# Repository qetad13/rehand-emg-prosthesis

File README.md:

# ReHand — EMG 기반 손가락 동작 인식 의수 제어 (v2)

> 졸업작품 · **2026.01 – 2026.10** · 4인 팀 (팀장) · v2는 2026-11에 추가

전완부 표면 근전도(sEMG) 4채널을 XIAO ESP32-S3로 1 kHz 샘플링하고, **보드 위에서 직접 추론**해 손가락 동작 8가지를 분류한 뒤 ESP-NOW로 의수 보드에 명령과 힘 세기를 보내는 시스템입니다.

이 브랜치(`v2-only`)에는 **스트리밍 특징 + 1D CNN(TCN)** 방식인 v2 파일만 있습니다.

| 브랜치 | 판단 방식 | 내용 |
|---|---|---|
| [`v2-only`](https://github.com/qetad13/rehand-emg-prosthesis/tree/v2-only) | 스트리밍 특징 + 1D CNN(TCN) | v2 파일만 있음 (지금 보고 있는 내용) |
| [`v1-stft-cnn`](https://github.com/qetad13/rehand-emg-prosthesis/tree/v1-stft-cnn) | STFT 스펙트로그램 + 2D CNN | 기존 버전만 있음 |
| [`main`](https://github.com/qetad13/rehand-emg-prosthesis) | 둘 다 | 기존 버전 위에 v2 추가 |

| 항목 | 내용 |
|---|---|
| 입력 | 표면 EMG 4채널, 1000 Hz, 12-bit ADC |
| 출력 | 휴식 / 엄지 / 검지 / 중지 / 약지 / 소지 / 주먹 / 집게 (8클래스) + 힘 세기 1~100 |
| MCU | Seeed XIAO ESP32-S3 (듀얼코어, 샘플링·추론 코어 분리) |
| 모델 | 25 ms마다 계산하는 특징 22개 + 과거만 보는 1D 합성곱 3층, 가중치 5,960개 |
| 통신 | ESP-NOW 양방향 (근전도 보드 ↔ 의수 보드 직접 연결, 자동 페어링) |
| 성능 | 미사용 순서 세션 기준 창 단위 정확도 **98.7%**, 실시간 제어 지연 중앙값 **226 ms** (25 ms마다 판단) |

> **실제 보드·의수에서의 동작 시험은 아직 하지 않았습니다.** 컴파일과 PC 대조 검증까지만 확인했습니다.
> 처음 올릴 때는 [docs/v2_guide.md](docs/v2_guide.md)의 "처음 올릴 때 확인 순서"를 따라 주세요.

사용 방법: [docs/v2_guide.md](docs/v2_guide.md) · 실험과 결과: [docs/v2_results.md](docs/v2_results.md)

---

## 시스템 구조

```mermaid
flowchart LR
    subgraph Arm["전완부"]
        S1[EMG 센서 ×4]
    end
    subgraph EMG["근전도 보드 (자체 PCB + XIAO ESP32-S3)"]
        ADC["ADC 1 kHz<br/>(Core 1)"] --> F["IIR 필터<br/>HPF 20 Hz + Notch 60 Hz"]
        F --> HOP["25 ms 누적값<br/>(크기 · 차분 · 영교차 · 채널 상관)"]
        HOP -->|큐| INF["특징 22개 → TCN 추론<br/>(Core 0, FreeRTOS task)"]
        INF --> V["확률 평활 + 문턱 + 휴식 게이트<br/>(오작동 억제)"]
        INF --> ST["힘 세기<br/>(최근 0.2초 크기 / 휴식 크기)"]
    end
    subgraph Hand["의수 보드 (XIAO ESP32-S3 + 서보 ×7)"]
        R[ESP-NOW 송수신] --> SV["서보 제어<br/>(힘 세기 → 속도 · 쥐는 힘)"]
    end
    S1 -->|Molex SPOX 3핀| ADC
    V -->|명령 1~8| R
    ST -->|힘 세기 1~100| R
    R -.->|"상태 (호밍 · 과열 · 전압)"| V

    subgraph PC["PC (오프라인)"]
        GUI["수집 GUI<br/>(PySide6)"] --> CSV[(CSV + 라벨 순서)]
        CSV --> TR["PyTorch 학습<br/>train_v2.py"]
        TR -->|"emg2_model.h<br/>emg2_test_vectors.h"| INF
        TR --> HC["host_check.py<br/>(C 코드 ↔ PyTorch 대조)"]
    end
    ADC -.->|MODE_RECORD, USB 시리얼| GUI
```

### 데이터 파이프라인

1. **수집** — 펌웨어를 `MODE_RECORD`로 올리고 GUI가 5초 힘주기 / 5초 쉬기를 안내하며 녹화 (1세션 = 8동작 × 10초 = 80초)
2. **전처리** — 4차 Butterworth HPF 20 Hz + 60 Hz 노치 (PC와 ESP32에서 **같은 SOS 계수**로 계산)
3. **특징** — 25 ms마다 채널별 로그 진폭(휴식 대비) · 주파수 비 2개 · 영교차율과 채널 쌍 상관 6개 = 22개. STFT 없이 누적합만으로 계산
4. **모델** — 과거만 보는 1D 합성곱 3층(폭 24/24/32, 커널 3, 팽창 1/2/4). 최근 0.375초를 보고 25 ms마다 확률 출력. 층마다 지난 결과를 버퍼에 두고 새 프레임만 계산
5. **라벨** — 화면 지시 시각이 아니라 근전도가 실제로 올라온·내려간 시점 기준. 전환 구간은 학습에서 제외
6. **출력 규칙** — 평활한 확률이 0.8 이상이면 켜기, 휴식 3번 연속이면 끄기, 최소 유지 0.1초, 휴식 게이트 1.5배. 손가락 → 다른 손가락은 휴식을 거쳐야 하고 주먹만 예외
7. **내보내기** — 가중치·필터 계수·판단 규칙을 C 헤더로 생성하고, PC 예측값을 테스트 벡터로 함께 내보냄

---

## 폴더 구조

```
rehand-emg-prosthesis/
├─ hardware/                 KiCad 프로젝트 (근전도 보드)
│  ├─ v1/                    초기 보드: 회로도 · PCB · gerber/
│  └─ v2/                    현재 보드 (배터리 · 버튼 추가): 회로도 · PCB · gerber/
├─ collector/                데이터 수집 GUI (PySide6 + pyserial)
│  └─ emg_collector_v4.py
├─ training/                 학습 + ESP32용 C 헤더 생성
│  ├─ train_v2.py            학습: python train_v2.py --cv
│  ├─ emg_data.py            데이터 읽기 · 필터 · 실시간 지표 (train_v2.py가 사용)
│  ├─ host_check.py          펌웨어 C 코드를 PC에서 PyTorch와 대조
│  ├─ data/Fixed/            고정 순서 세션 15개 (학습 / 교차검증)
│  ├─ data/Random/           무작위 순서 세션 5개 (시험 전용)
│  └─ output_v2/             학습 결과 (report, 그림, 모델)
├─ firmware/                 Arduino (XIAO ESP32-S3)
│  ├─ emg_board_v2/          근전도 보드: 녹화 · 점검 · 실시간 판단 · 재생 · 자가 점검
│  └─ hand_board_v2/         의수 보드: 자세 표 · 힘 세기 비례 제어 · 호밍 · 서보 감시
└─ docs/
   ├─ v2_guide.md            사용 안내
   ├─ v2_results.md          결과와 실험 기록
   └─ images/                결과 그림 · 회로도
```

`hardware/v1`, `hardware/v2`는 PCB 버전이고, 판단 방식의 v1/v2와는 관계가 없습니다.

---

## 하드웨어

<p align="center">

  <br><sub>왼쪽 PCB v1 · 오른쪽 PCB v2 (현재)</sub>
</p>

| | PCB v1 | PCB v2 (현재) |
|---|---|---|
| 크기 | 28.75 × 40 mm | 33.2 × 40 mm |
| MCU 실장 | XIAO ESP32-S3 DIP 풋프린트 | XIAO ESP32-S3 **SMD** 풋프린트 (하단 BAT 패드 사용) |
| 센서 입력 | Molex SPOX 3핀 ×4 (신호 / 3V3 / GND → A0~A3) | 동일 |
| 전원 | USB | **J5 PicoBlade 2핀** → XIAO BAT 패드 (배터리 연결) |
| 입력 버튼 | 없음 | **SW1 · SW2** (D7 · D8), 풀업 저항 + 디바운스 커패시터 (0805) |
| 회로도 | [schematic_v1.svg](docs/images/schematic_v1.svg) | [schematic_v2.svg](docs/images/schematic_v2.svg) |

버튼 동작 (자세한 내용과 LED 표시는 [docs/v2_guide.md](docs/v2_guide.md)):

| 버튼 | 짧게 | 3초 |
|---|---|---|
| SW1 | 근전도 모드 ↔ 매크로 모드 (뗄 때 바뀜) | 사용자 보정 시작 |
| SW2 | 근전도 모드: 잠금 켜기/끄기 · 매크로 모드: 다음 동작 | 의수 호밍 |

스위치가 없는 보드에서는 시리얼 키(`1 2 h c x l ?`)나 BOOT 버튼으로 대신 조작합니다.

---

## 성능

평가는 **학습에 쓰지 않은 Random 세션 5개**(동작 순서를 무작위로 섞어 녹화, 총 6.7분)로 했습니다. 설정은 고정 순서 15세션의 5겹 교차검증만으로 골랐습니다. 비교 대상 v1은 [`v1-stft-cnn`](https://github.com/qetad13/rehand-emg-prosthesis/tree/v1-stft-cnn) 브랜치의 STFT + 2D CNN 방식입니다.

| Random 5세션 | v1 | v2 (이 브랜치) |
|---|---|---|
| 창 단위 정확도 (8클래스) | 96.4% | **98.7%** |
| 창 단위 정확도 (휴식 제외 7동작) | 95.1% | **97.7%** |
| 수축 구간 다수결 | 38/40 | 39/40 |
| 근전도 시작 → 올바른 출력 (중앙값 / 90%) | 356 / 820 ms | **226** / 744 ms |
| 힘 뺀 뒤 출력 해제 (중앙값) | 169 ms | **94 ms** |
| 동작 인식 성공 / 놓침 | 34 / 1 | 35 / 0 |
| 잘못된 손가락 출력 (6.7분) | 3회 | 1회 |
| 휴식 중 오작동 비율 | 0.1% | 0.26% |
| 판단 주기 | 100 ms | 25 ms |
| 1초당 곱셈 수 | 약 300만 | 약 23만 |

클래스별: 휴식 100%, 엄지 100%, 검지 100%, 중지 99%, 약지 100%, 소지 99%, 주먹 100%, 집게 86%

| 교차검증 (고정 순서 15세션, 20분) | v1 | v2 |
|---|---|---|
| 창 단위 정확도 | 97.6% | **99.1%** |
| 제어 지연 중앙값 / 90% | 298 / 586 ms | **220 / 471 ms** |
| 인식 성공 / 놓침 | 100 / 4 | 104 / 0 |
| 잘못된 손가락 출력 | 28회 | **3회** |
| 휴식 중 오작동 비율 | 0.52% | 0.09% |

알아 둘 점

- 휴식 중 오작동 비율은 Random에서 v1보다 조금 높습니다 (교차검증에서는 낮음).
- 집게가 86%로 가장 약합니다.
- 20세션이 모두 한 번 붙인 상태에서 녹화되어, 전극을 다시 붙였을 때의 성능은 확인하지 못했습니다. 이를 줄이기 위해 사용자 보정(약 40초)을 넣었습니다.
- 지연에는 무선 전송과 서보 반응 시간이 포함되어 있지 않습니다.

실험 내용(특징별 기여, 힘 세기 변화, 보정 효과)은 [docs/v2_results.md](docs/v2_results.md)에 있습니다.

---

## 주요 기능

- **근전도 보드** ([firmware/emg_board_v2](firmware/emg_board_v2))
  - 모드 5개: 녹화(`MODE_RECORD`) · 센서 점검(`MODE_CHECK`) · 실시간 판단(`MODE_RUN`) · 저장 데이터 재생(`MODE_REPLAY`) · 자가 점검(`MODE_SELFTEST`)
  - 사용자 보정: 의수가 동작을 하나씩 보여 주면 따라 하는 방식으로 채널별 이득과 동작별 힘 기준을 다시 맞추고 보드에 저장
  - 잠금 모드: 쥔 상태를 유지한 채 힘을 빼도 풀리지 않게 함
  - 의수 상태(연결 · 호밍 중 · 과열 · 전압 · 서보 응답)를 LED로 표시
- **의수 보드** ([firmware/hand_board_v2](firmware/hand_board_v2))
  - 힘 세기에 비례한 속도와 쥐는 힘, 움직이는 동안 계속 반영
  - "네 손가락 먼저 → 엄지" 순서를 기다리는 동안에도 명령과 무선 수신이 멈추지 않음
  - 호밍을 별도 태스크로 분리, 자세를 표 한 줄로 추가·수정
  - 서보 온도 · 전압 · 응답을 감시해 근전도 보드에 알림
  - 처음 연결된 근전도 보드의 주소를 저장하고 다른 송신기의 명령은 무시 (시리얼 `p` 또는 BOOT 3초로 해제, 암호화는 없음)
- **PC 대조 검증** ([training/host_check.py](training/host_check.py))
  - 펌웨어의 `emg2.cpp`를 PC에서 그대로 컴파일해 Random 세션 전체(32,014프레임)를 PyTorch와 비교: 확률 차이 최대 8.3e-07, 최종 출력 차이 0

---

## 실행 방법

### 1. 설치
```bash
pip install -r training/requirements.txt -r collector/requirements.txt
```

### 2. 데이터 수집
1. `firmware/emg_board_v2/emg_board_v2.ino`에서 `#define RUN_MODE MODE_CHECK`로 업로드 → 채널 상태 확인
2. `MODE_RECORD`로 업로드 후 `python collector/emg_collector_v4.py`
3. 고정 순서는 `training/data/Fixed/`, 무작위 순서는 `training/data/Random/`에 저장 (순서는 `_order.txt`로 자동 기록)

### 3. 학습과 검증
```bash
python training/train_v2.py --cv
```
```bash
python training/host_check.py
```
`emg2_model.h`, `emg2_test_vectors.h`가 `firmware/emg_board_v2`에 자동 복사됩니다. `host_check.py`는 C++ 컴파일러가 필요합니다 (없으면 `pip install ziglang`).

### 4. 업로드
| 스케치 | 용도 |
|---|---|
| `emg_board_v2` (`MODE_SELFTEST`) | PC 결과와 일치 여부 확인 (`8 / 8 통과`), 판단 1회 계산 시간 |
| `emg_board_v2` (`MODE_RUN`) | 실시간 판단 + ESP-NOW 전송 |
| `emg_board_v2` (`MODE_REPLAY`) | 센서 없이 저장 데이터로 판단 흐름 확인 |
| `hand_board_v2` | 의수 제어 (시리얼에서 `숫자`, `s숫자`, `?`로 단독 시험) |

Arduino IDE 설정: 보드 `XIAO_ESP32S3`, `USB CDC On Boot: Enabled`

---

## 변경 이력

| 날짜 | 변경 내용 |
|---|---|
| 2026-11-12 | **연결 상대 고정**: 의수가 처음 연결된 근전도 보드의 주소를 저장하고 다른 송신기의 명령은 무시. 의수 시리얼 `p` 또는 BOOT 3초로 해제. 암호화는 아직 없음 ([#1](https://github.com/qetad13/rehand-emg-prosthesis/issues/1)) |
| 2026-11-12 | **v2**: 스트리밍 특징 + TCN 판단 방식(`train_v2.py`, `emg_board_v2`), 의수 보드 v2(`hand_board_v2`: 힘 세기 비례 제어, 양방향 연결, 호밍 태스크), 사용자 보정, 잠금 모드, PC 대조 검증(`host_check.py`) |
| 2026-09-30 | **PCB v2**: XIAO SMD 실장, 배터리 커넥터, 버튼 2개(풀업 + RC 디바운스) 추가 |

그 전의 개발 과정과 트러블슈팅 기록은 [`v1-stft-cnn`](https://github.com/qetad13/rehand-emg-prosthesis/tree/v1-stft-cnn) 브랜치의 README에 있습니다.

---

## 기술 스택
`Python` `PyTorch` `NumPy/SciPy` `PySide6` · `C/C++ (Arduino, FreeRTOS)` · `KiCad`

## 연락처

| 항목 | 내용 |
|---|---|
| 소속 | 전자공학과 |
| 이메일 | [kjoonh1@gmail.com](mailto:kjoonh1@gmail.com) |
| GitHub | [@qetad13](https://github.com/qetad13) |

## 라이선스 / 출처
- [MIT License](LICENSE) (아래 외부 코드는 각 원본 라이선스를 따름)
- `firmware/emg_board_v2/EMGFilters.*`: OYMotion Inc. (BSD-3-Clause), 채널별 상태 분리 수정

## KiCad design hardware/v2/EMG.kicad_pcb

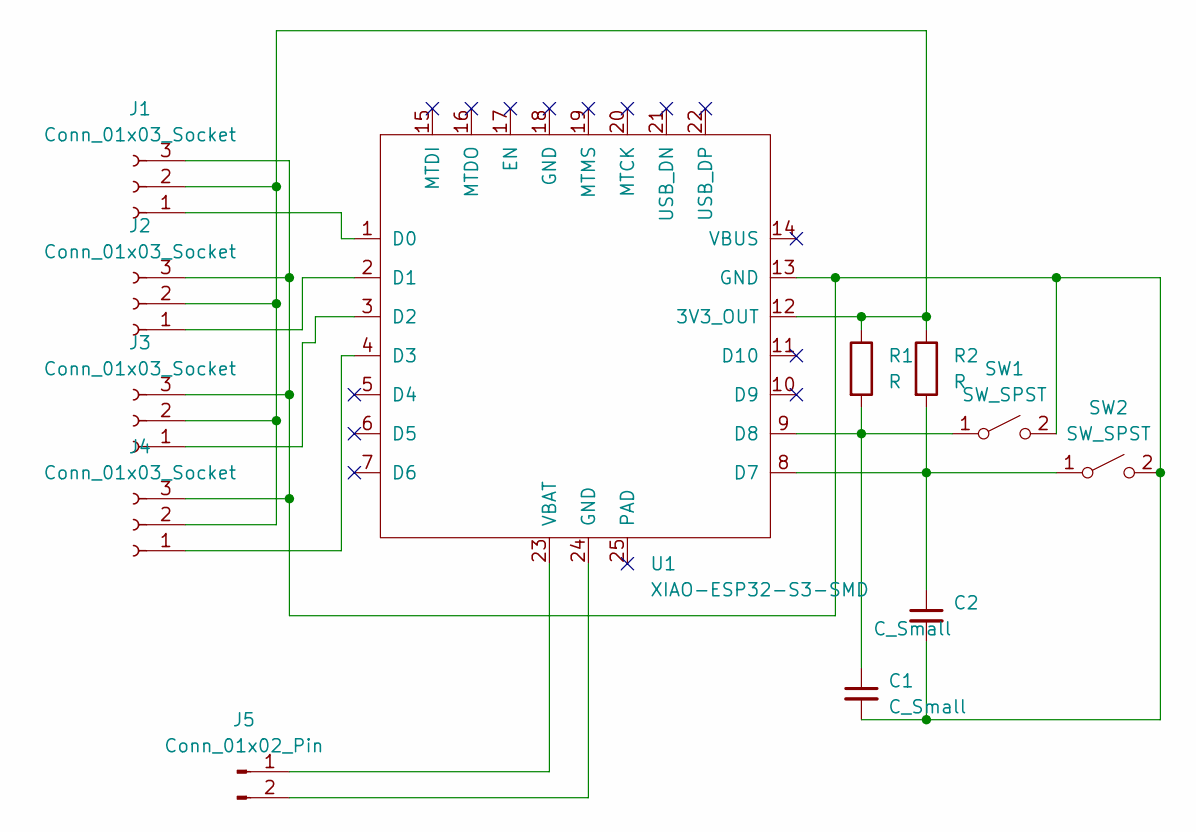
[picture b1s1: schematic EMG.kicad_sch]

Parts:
C1, C2: C_Small; C_0805_2012Metric
J1, J2, J3, J4: Conn_01x03_Socket; Molex_SPOX_5267-03A_1x03_P2.50mm_Vertical
J5: Conn_01x02_Pin; Molex_PicoBlade_53261-0271_1x02-1MP_P1.25mm_Horizontal
R1, R2: R; R_0805_2012Metric
SW1, SW2: SW_SPST; PinHeader_1x02_P2.54mm_Vertical
U1: XIAO-ESP32-S3-SMD

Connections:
unnamed: J1.1, U1.1 (D0)
unnamed 1: J1.2, J2.2, J3.2, J4.2, R1.1, R2.1, U1.12 (3V3_OUT); also elsewhere on the board
unnamed: C1.2, C2.2, J1.3, J2.3, J3.3, J4.3, SW1.2 (B), SW2.2 (B), U1.13 (GND)
unnamed: J2.1, U1.2 (D1)
unnamed: J3.1, U1.3 (D2)
unnamed: J4.1, U1.4 (D3)
unnamed: J5.1, U1.23 (VBAT)
unnamed: J5.2, U1.24 (GND)
unnamed 8: C1.1, R1.2, SW1.1 (A), U1.9 (D8); also elsewhere on the board
unnamed: C2.1, R2.2, SW2.1 (A), U1.8 (D7)

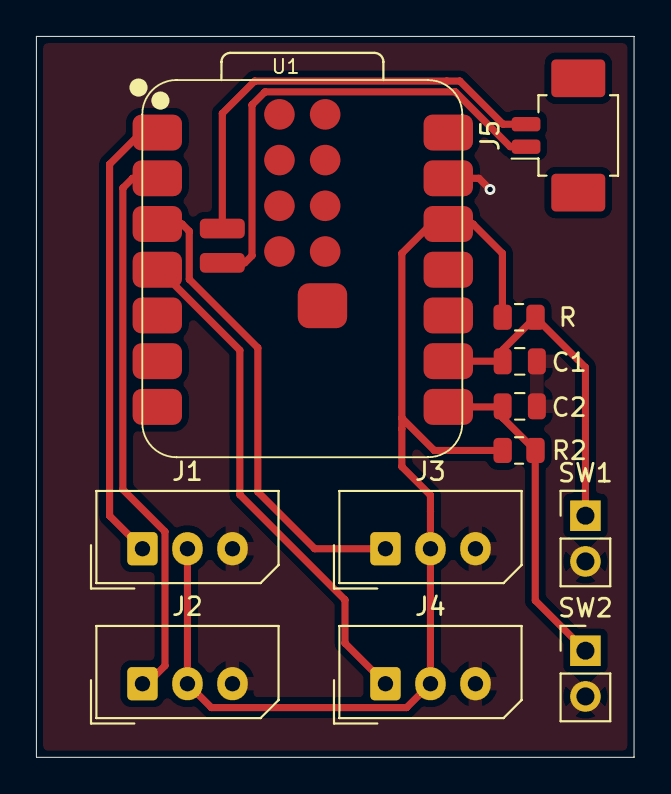
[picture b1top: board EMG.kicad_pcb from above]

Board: 2 copper layers, 33.2 x 40.0 mm, 12 parts (0 on the bottom side), 10 nets.

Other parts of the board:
R: R; R_0805_2012Metric

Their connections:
unnamed 1: R.1; also elsewhere on the board
unnamed 8: R.2; also elsewhere on the board
